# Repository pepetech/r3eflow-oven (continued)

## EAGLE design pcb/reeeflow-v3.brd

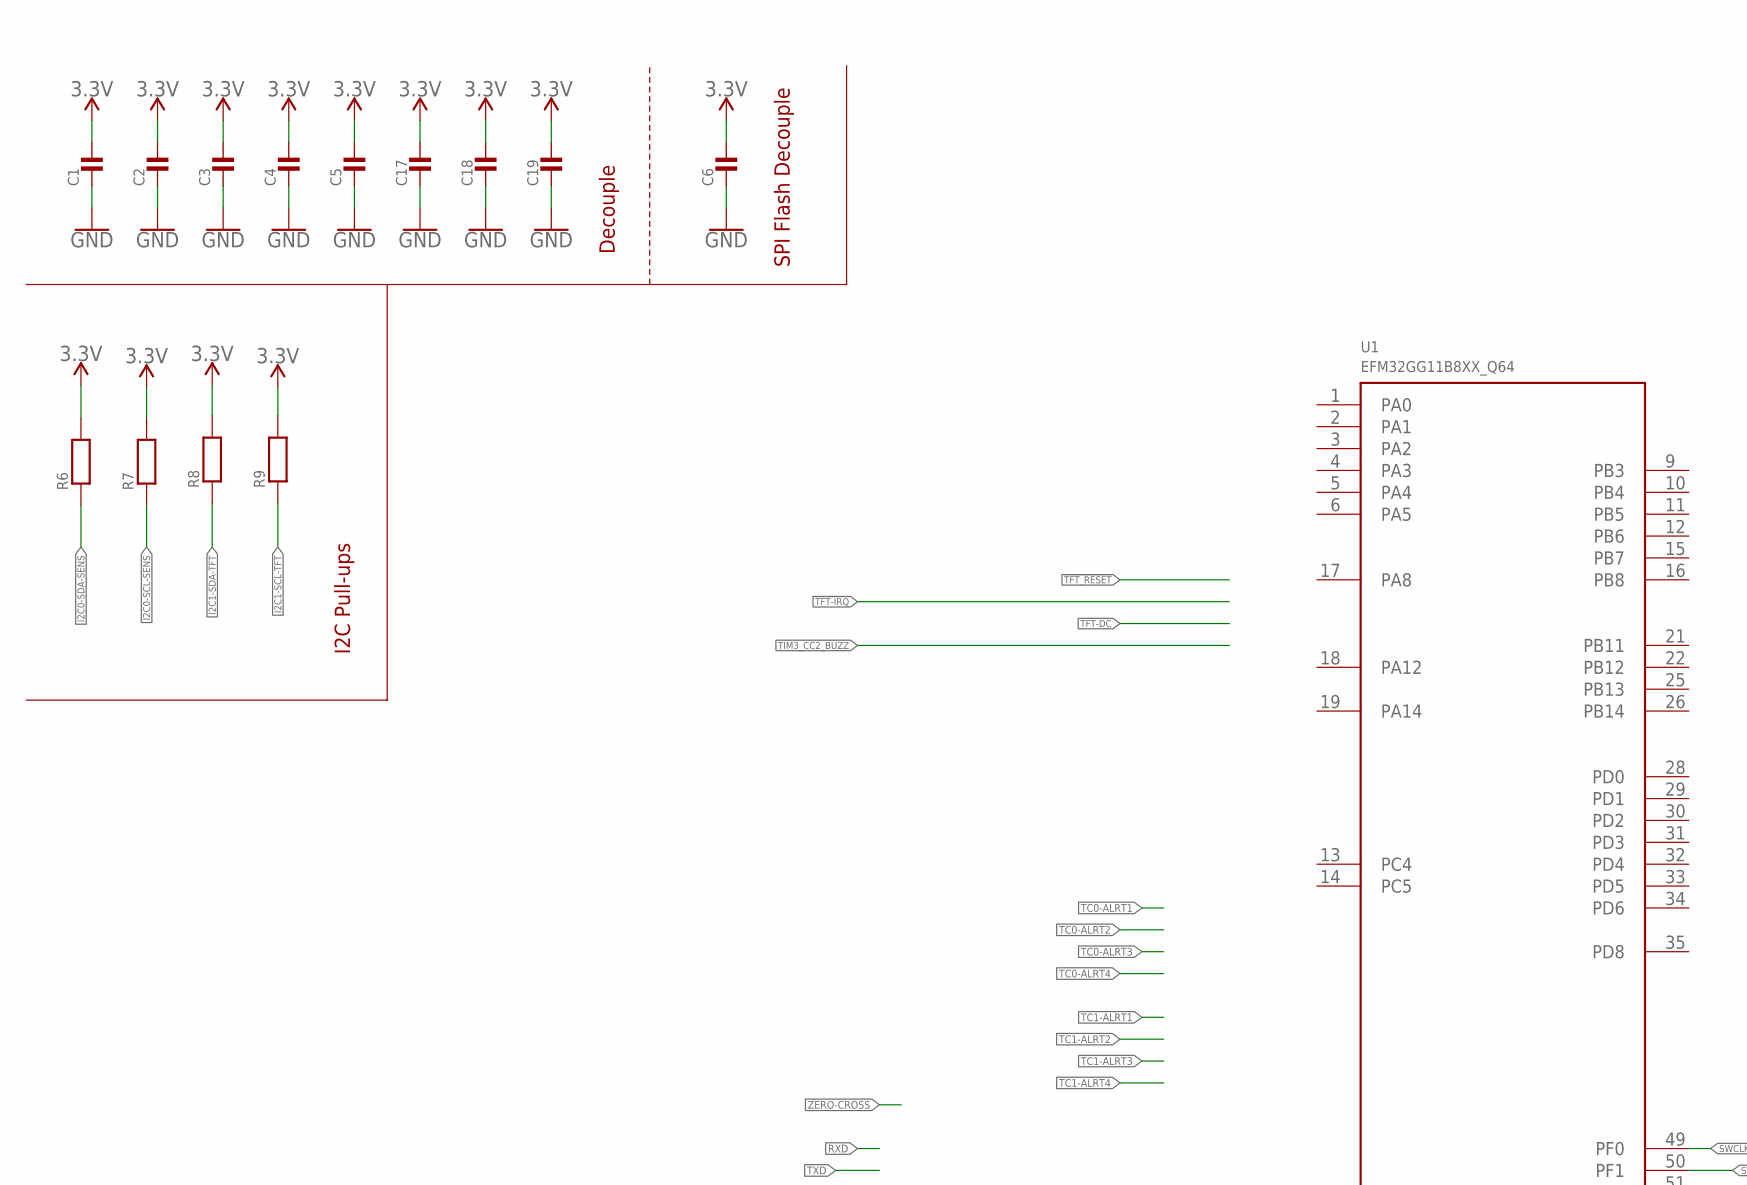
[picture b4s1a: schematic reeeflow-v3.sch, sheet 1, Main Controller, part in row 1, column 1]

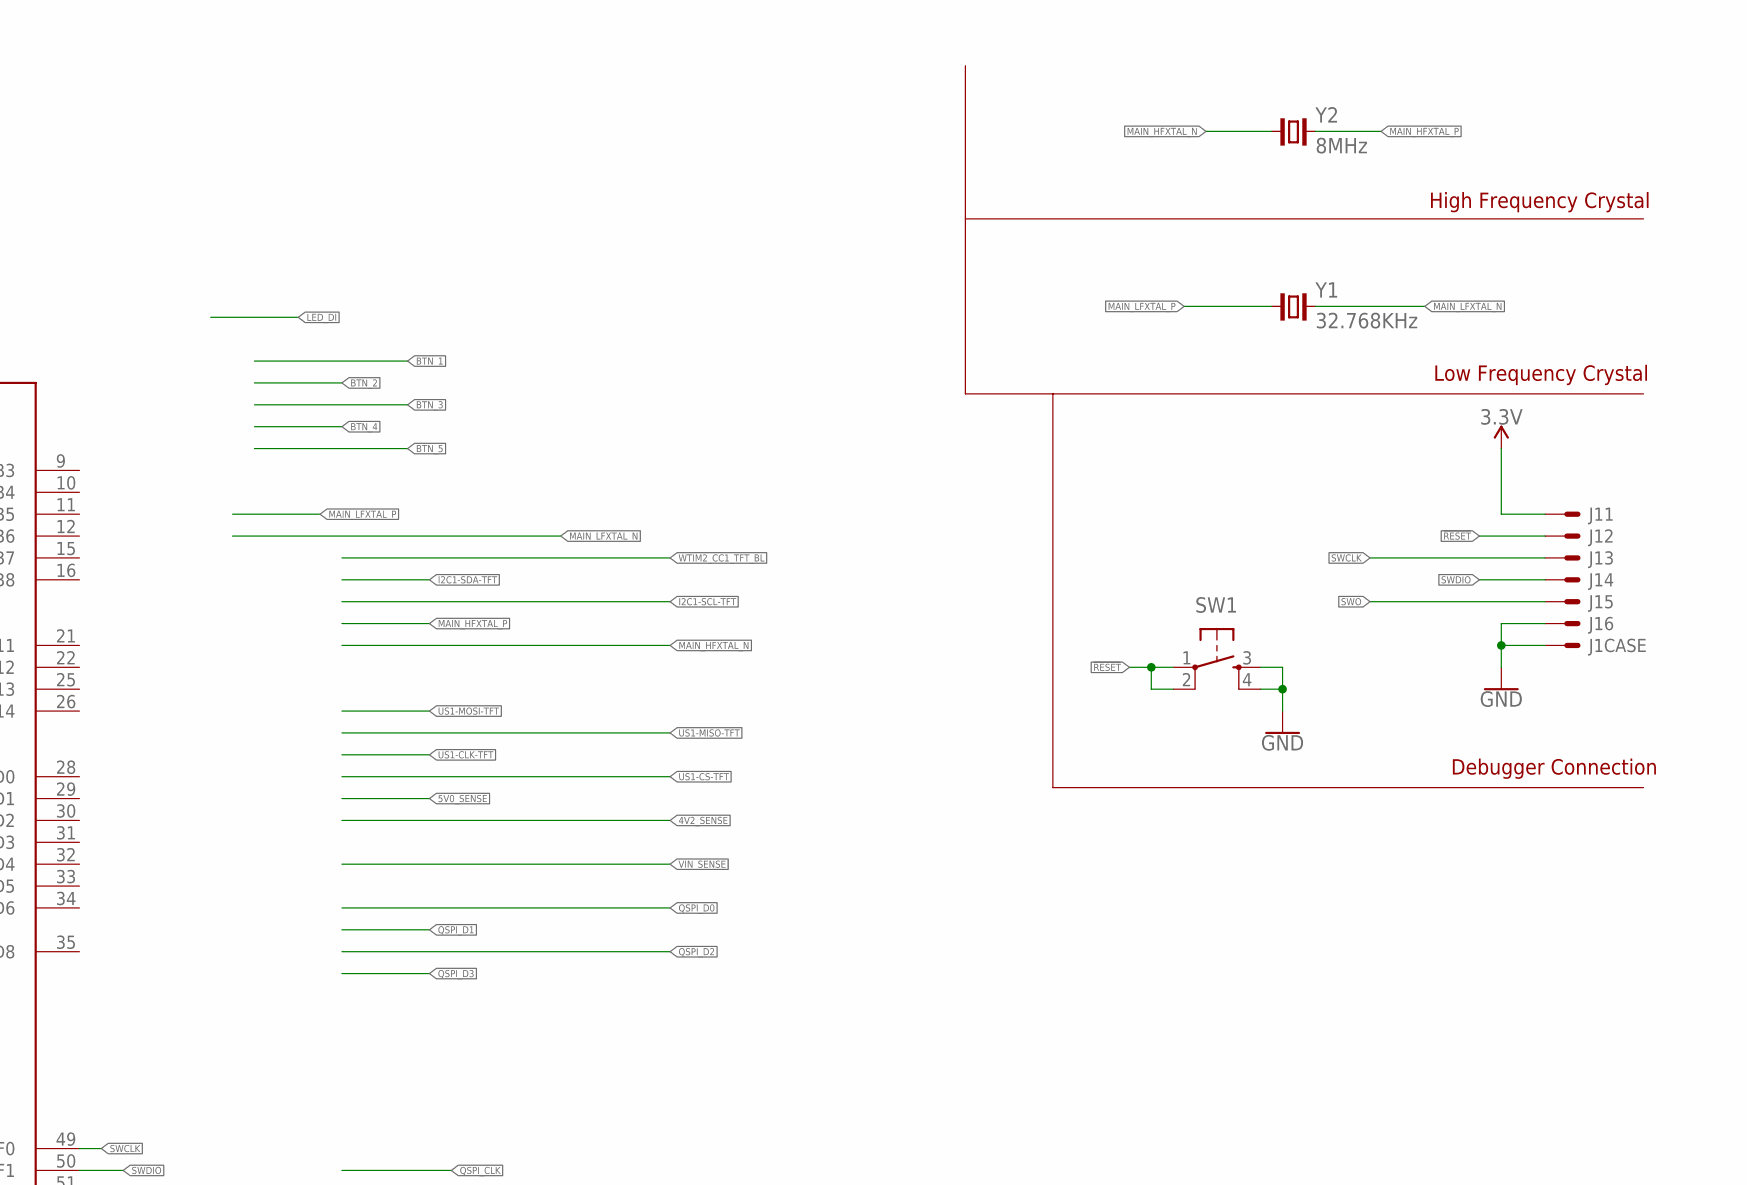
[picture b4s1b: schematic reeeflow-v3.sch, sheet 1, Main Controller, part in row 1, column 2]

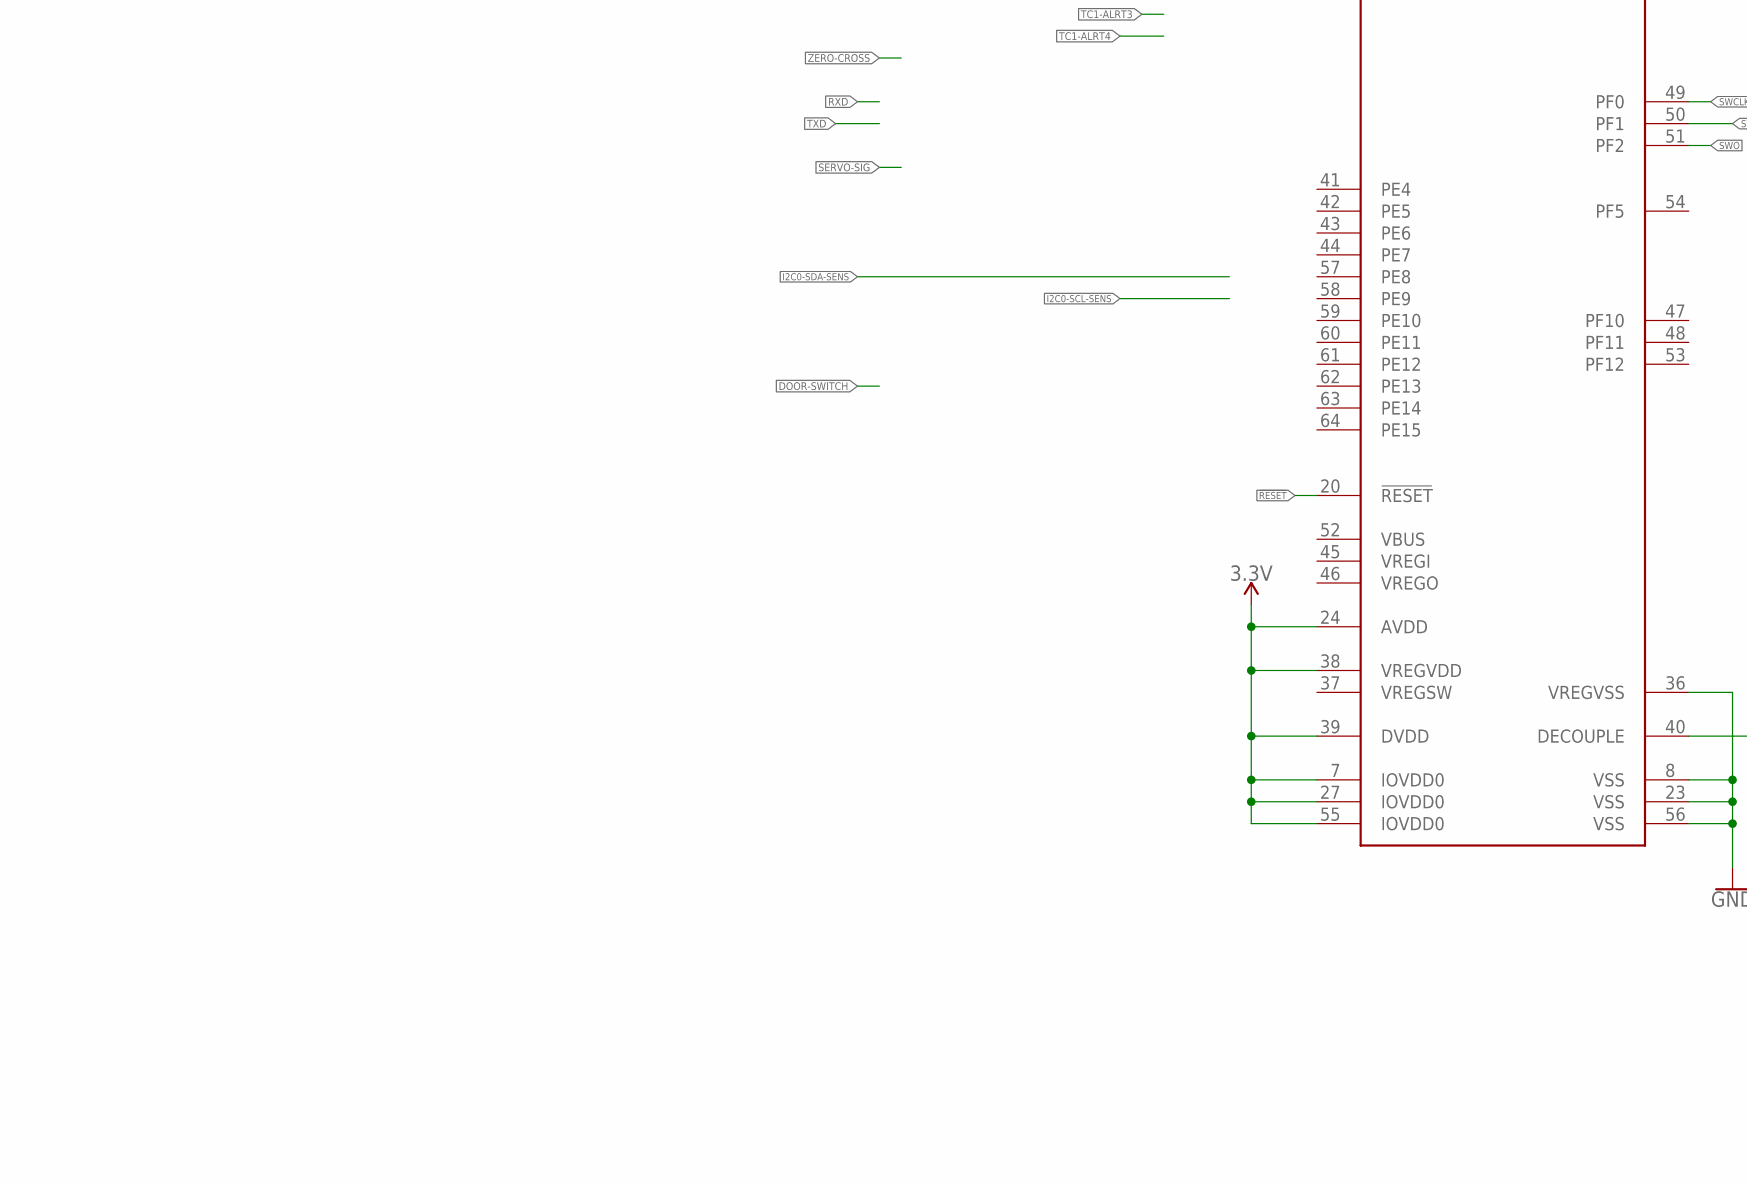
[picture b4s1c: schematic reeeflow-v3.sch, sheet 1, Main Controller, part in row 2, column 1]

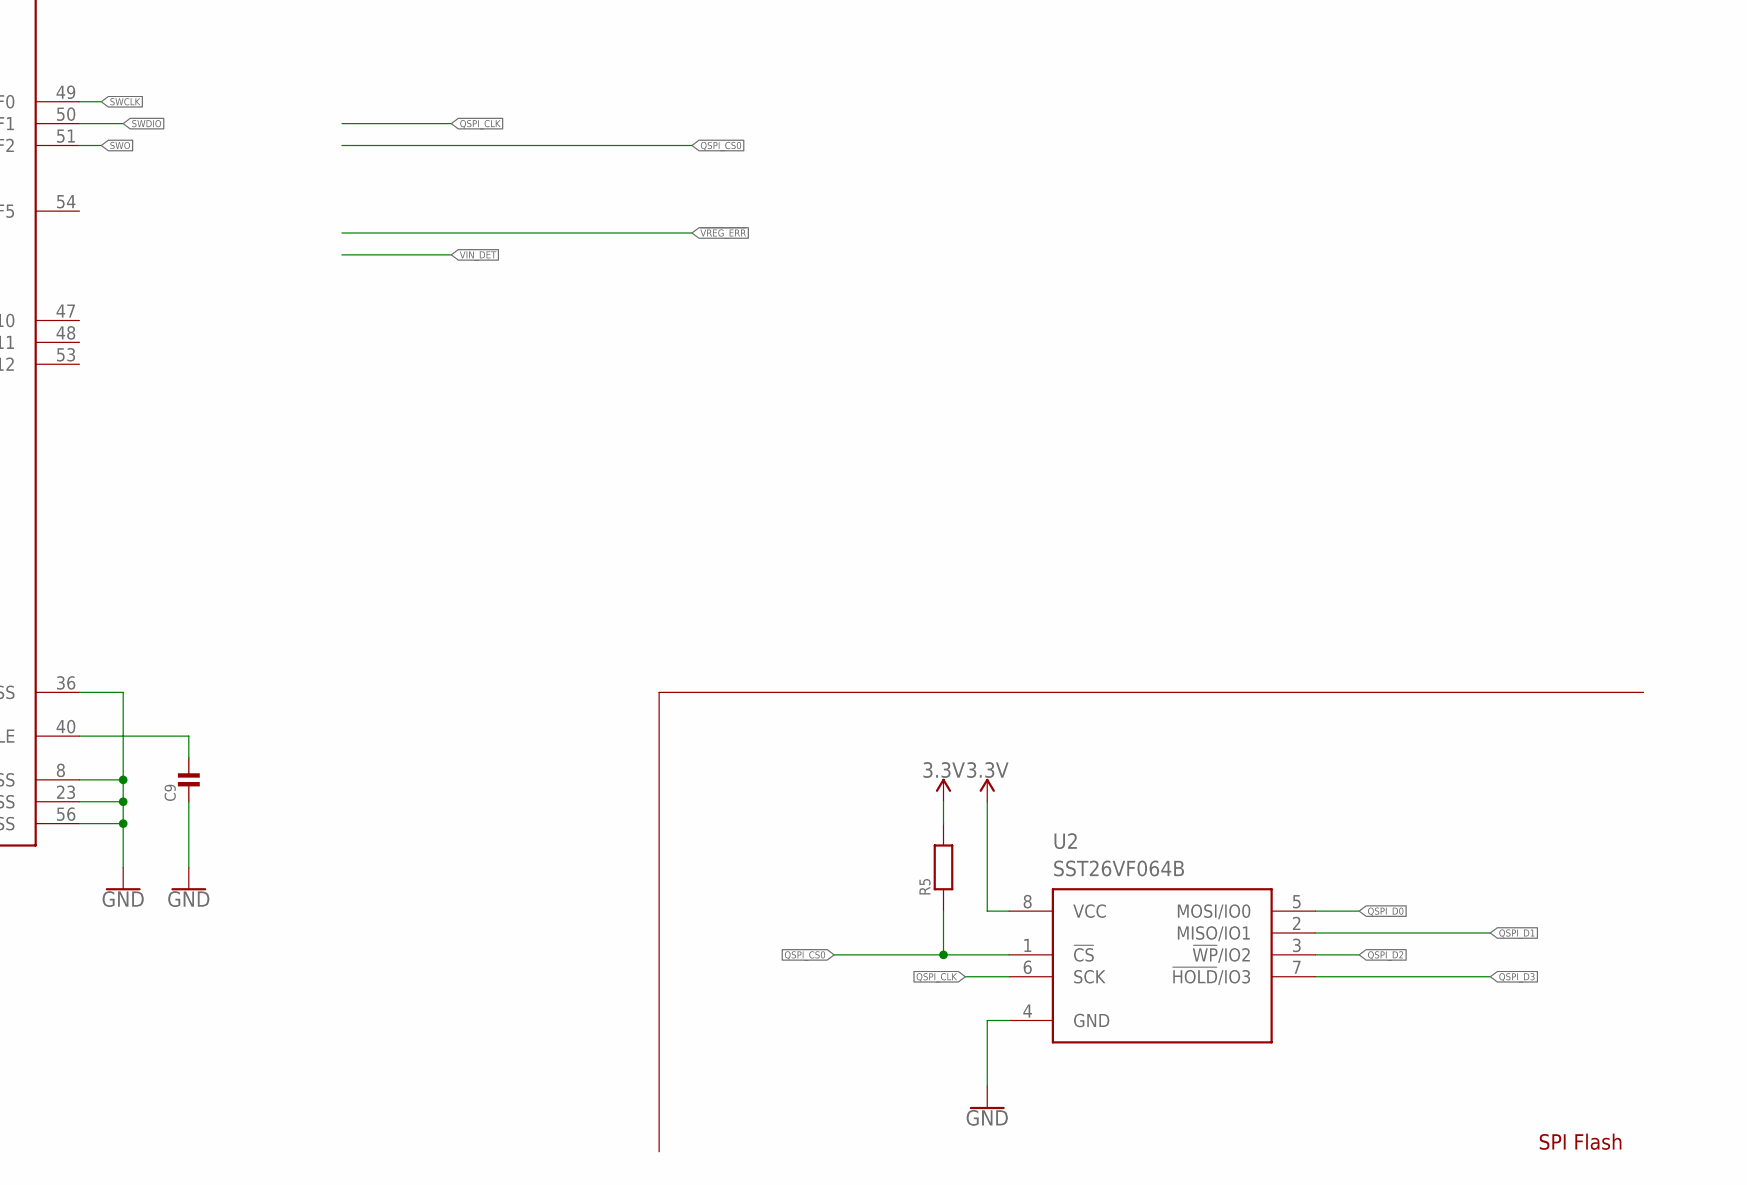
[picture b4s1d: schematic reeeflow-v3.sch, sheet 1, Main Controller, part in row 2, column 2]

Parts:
C1, C2, C3, C4, C5, C6, C9, C17, C18, C19: MLCC0603; 0603_WAVE
J1: SH-6; SM06B-SSR-H-TB
R5, R6, R7, R8, R9: RESISTOR0603; 0603_WAVE
SW1: PUSH_BUTTON
U1: EFM32GG11B8XX_Q64; QFP64
U2: SST26VF064B; WSOIC8
Y1: 32.768KHz; CM200S
Y2: 8MHz; 2-SMD-5X3

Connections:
3.3V: C1.P$1, C2.P$1, C3.P$1, C4.P$1, C5.P$1, C6.P$1, C17.P$1, C18.P$1, C19.P$1, J1.1, R5.P$2, R6.P$2, R7.P$2, R8.P$2, R9.P$2, U1.7 (IOVDD0), U1.24 (AVDD), U1.27 (IOVDD0), U1.38 (VREGVDD), U1.39 (DVDD), U1.55 (IOVDD0), U2.8 (VCC); also elsewhere on the board
!RESET: J1.2, SW1.1, SW1.2, U1.20 (!RESET)
GND: C1.P$2, C2.P$2, C3.P$2, C4.P$2, C5.P$2, C6.P$2, C9.P$2, C17.P$2, C18.P$2, C19.P$2, J1.6, J1.FIT@1, J1.FIT@2, SW1.3, SW1.4, U1.8 (VSS), U1.23 (VSS), U1.36 (VREGVSS), U1.56 (VSS), U2.4 (GND); also elsewhere on the board
I2C0-SCL-SENS: R7.P$1; also elsewhere on the board
I2C0-SDA-SENS: R6.P$1; also elsewhere on the board
I2C1-SCL-TFT: R9.P$1; also elsewhere on the board
I2C1-SDA-TFT: R8.P$1; also elsewhere on the board
MAIN_HFXTAL_N: Y2.1
MAIN_HFXTAL_P: Y2.2
MAIN_LFXTAL_N: Y1.4 (2)
MAIN_LFXTAL_P: Y1.1
unnamed: C9.P$1, U1.40 (DECOUPLE)
QSPI_CLK: U2.6 (SCK)
QSPI_CS0: R5.P$1, U2.1 (!CS!)
QSPI_D0: U2.5 (MOSI/IO0)
QSPI_D1: U2.2 (MISO/IO1)
QSPI_D2: U2.3 (!WP!/IO2)
QSPI_D3: U2.7 (!HOLD!/IO3)
SWCLK: J1.3, U1.49 (PF0)
SWDIO: J1.4, U1.50 (PF1)
SWO: J1.5, U1.51 (PF2)

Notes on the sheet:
High Frequency Crystal
Low Frequency Crystal
Decouple
I2C Pull-ups
Debugger Connection
SPI Flash
SPI Flash Decouple

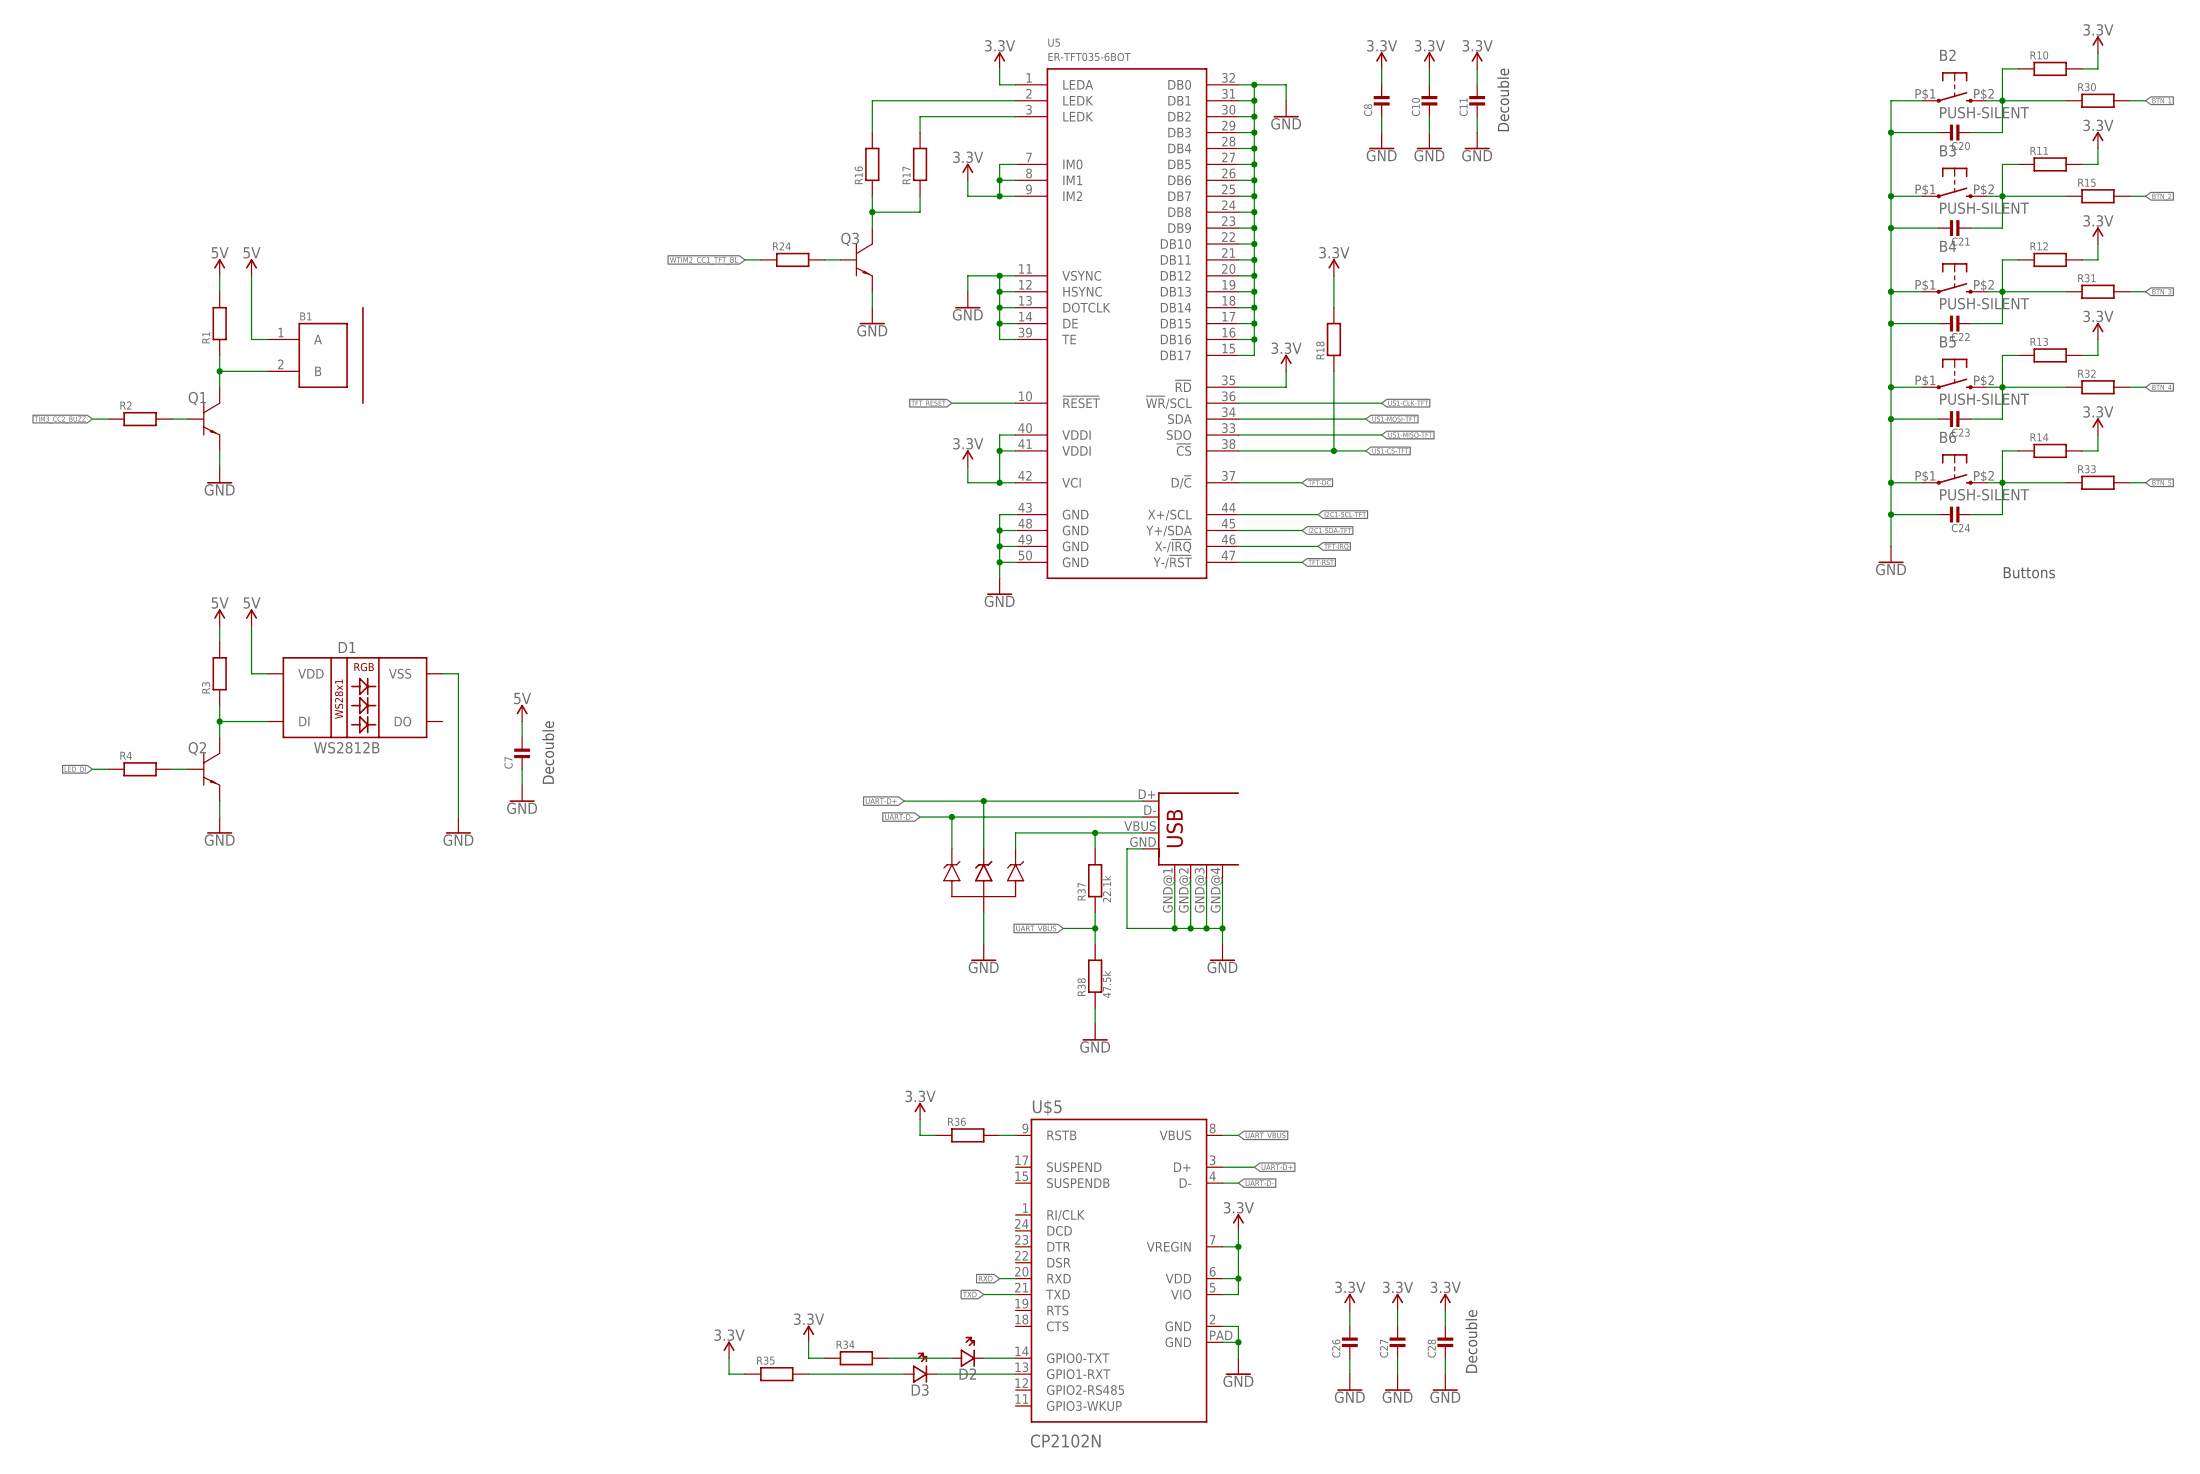
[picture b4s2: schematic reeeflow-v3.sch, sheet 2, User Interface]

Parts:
B1: PKLCS1212E2400-R1; BUZZ_PIEZO_SMD
B2, B3, B4, B5, B6: PUSH-SILENT; SILENT_BUT
C7, C8, C10, C11, C20, C21, C22, C23, C24, C26, C27, C28: MLCC0603; 0603_WAVE
D1: WS2812B
D2, D3: SML-D12; 0603_LED
D4: SP0503BAHT; SOT143
Q1, Q2, Q3: BC817-40; SOT-23-3
R1, R2, R3, R4, R10, R11, R12, R13, R14, R15, R16, R17, R18, R24, R30, R31, R32, R33, R34, R35, R36: RESISTOR0603; 0603_WAVE
R37: 22.1k; 0603_WAVE
R38: 47.5k; 0603_WAVE
U5: ER-TFT035-6BOT; ZIF50-TFT_BACK
U$5: CP2102N; QFN24
U$6: USB-SHIELD; USB-M-S1

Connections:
3.3V: C8.P$1, C10.P$1, C11.P$1, C26.P$1, C27.P$1, C28.P$1, R10.P$2, R11.P$2, R12.P$2, R13.P$2, R14.P$2, R18.P$2, R34.P$1, R35.P$1, R36.P$1, U5.1 (LEDA), U5.7 (IM0), U5.8 (IM1), U5.9 (IM2), U5.35 (!RD), U5.40 (VDDI), U5.41 (VDDI), U5.42 (VCI), U$5.5 (VIO), U$5.6 (VDD), U$5.7 (VREGIN); also elsewhere on the board
5V: B1.1 (A), C7.P$1, D1.1 (VDD), R1.P$2, R3.P$2; also elsewhere on the board
!TFT-IRQ: U5.46 (X-/!IRQ!)
!TFT-RST: U5.47 (Y-/!RST!)
!TFT_RESET: U5.10 (!RESET)
BTN_1: R30.P$2
BTN_2: R15.P$2
BTN_3: R31.P$2
BTN_4: R32.P$2
BTN_5: R33.P$2
GND: B2.P$1 (1), B3.P$1 (1), B4.P$1 (1), B5.P$1 (1), B6.P$1 (1), C7.P$2, C8.P$2, C10.P$2, C11.P$2, C20.P$1, C21.P$1, C22.P$1, C23.P$1, C24.P$1, C26.P$2, C27.P$2, C28.P$2, D1.3 (VSS), D4.1, Q1.P$2 (EM2), Q2.P$2 (EM2), Q3.P$2 (EM2), R38.P$1, U5.11 (VSYNC), U5.12 (HSYNC), U5.13 (DOTCLK), U5.14 (DE), U5.15 (DB17), U5.16 (DB16), U5.17 (DB15), U5.18 (DB14), U5.19 (DB13), U5.20 (DB12), U5.21 (DB11), U5.22 (DB10), U5.23 (DB9), U5.24 (DB8), U5.25 (DB7), U5.26 (DB6), U5.27 (DB5), U5.28 (DB4), U5.29 (DB3), U5.30 (DB2), U5.31 (DB1), U5.32 (DB0), U5.39 (TE), U5.43 (GND), U5.48 (GND), U5.49 (GND), U5.50 (GND), U$5.2 (GND), U$5.PAD (GND), U$6.GND, U$6.GND@1 (GND), U$6.GND@2 (GND), U$6.GND@3 (GND), U$6.GND@4 (GND); also elsewhere on the board
I2C1-SCL-TFT: U5.44 (X+/SCL); also elsewhere on the board
I2C1-SDA-TFT: U5.45 (Y+/SDA); also elsewhere on the board
LED_DI: R4.P$1
unnamed: B2.P$2 (3), C20.P$2, R10.P$1, R30.P$1
unnamed: D4.4, R37.P$2, U$6.VBUS
unnamed: B3.P$2 (3), C21.P$2, R11.P$1, R15.P$1
unnamed: B4.P$2 (3), C22.P$2, R12.P$1, R31.P$1
unnamed: Q2.P$1 (BA1), R4.P$2
unnamed: D1.4 (DI), Q2.P$3 (C03), R3.P$1
unnamed: B5.P$2 (3), C23.P$2, R13.P$1, R32.P$1
unnamed: D3.P$1 (CA), U$5.13 (GPIO1-RXT)
unnamed: B6.P$2 (3), C24.P$2, R14.P$1, R33.P$1
unnamed: D2.P$1 (CA), U$5.14 (GPIO0-TXT)
unnamed: D2.P$2 (AN), R34.P$2
unnamed: B1.2 (B), Q1.P$3 (C03), R1.P$1
unnamed: Q1.P$1 (BA1), R2.P$2
unnamed: D3.P$2 (AN), R35.P$2
unnamed: R16.P$2, U5.2 (LEDK)
unnamed: R17.P$2, U5.3 (LEDK)
unnamed: Q3.P$3 (C03), R16.P$1, R17.P$1
unnamed: Q3.P$1 (BA1), R24.P$2
unnamed: R36.P$2, U$5.9 (RSTB)
RXD: U$5.20 (RXD)
TFT-DC: U5.37 (D/!C!)
TIM3_CC2_BUZZ: R2.P$1
TXD: U$5.21 (TXD)
UART-D+: D4.3, U$5.3 (D+), U$6.D+
UART-D-: D4.2, U$5.4 (D-), U$6.D-
UART_VBUS: R37.P$1, R38.P$2, U$5.8 (VBUS)
US1-CLK-TFT: U5.36 (!WR!/SCL)
US1-CS-TFT: R18.P$1, U5.38 (!CS)
US1-MISO-TFT: U5.33 (SDO)
US1-MOSI-TFT: U5.34 (SDA)
WTIM2_CC1_TFT_BL: R24.P$1

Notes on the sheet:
Decouble
Buttons

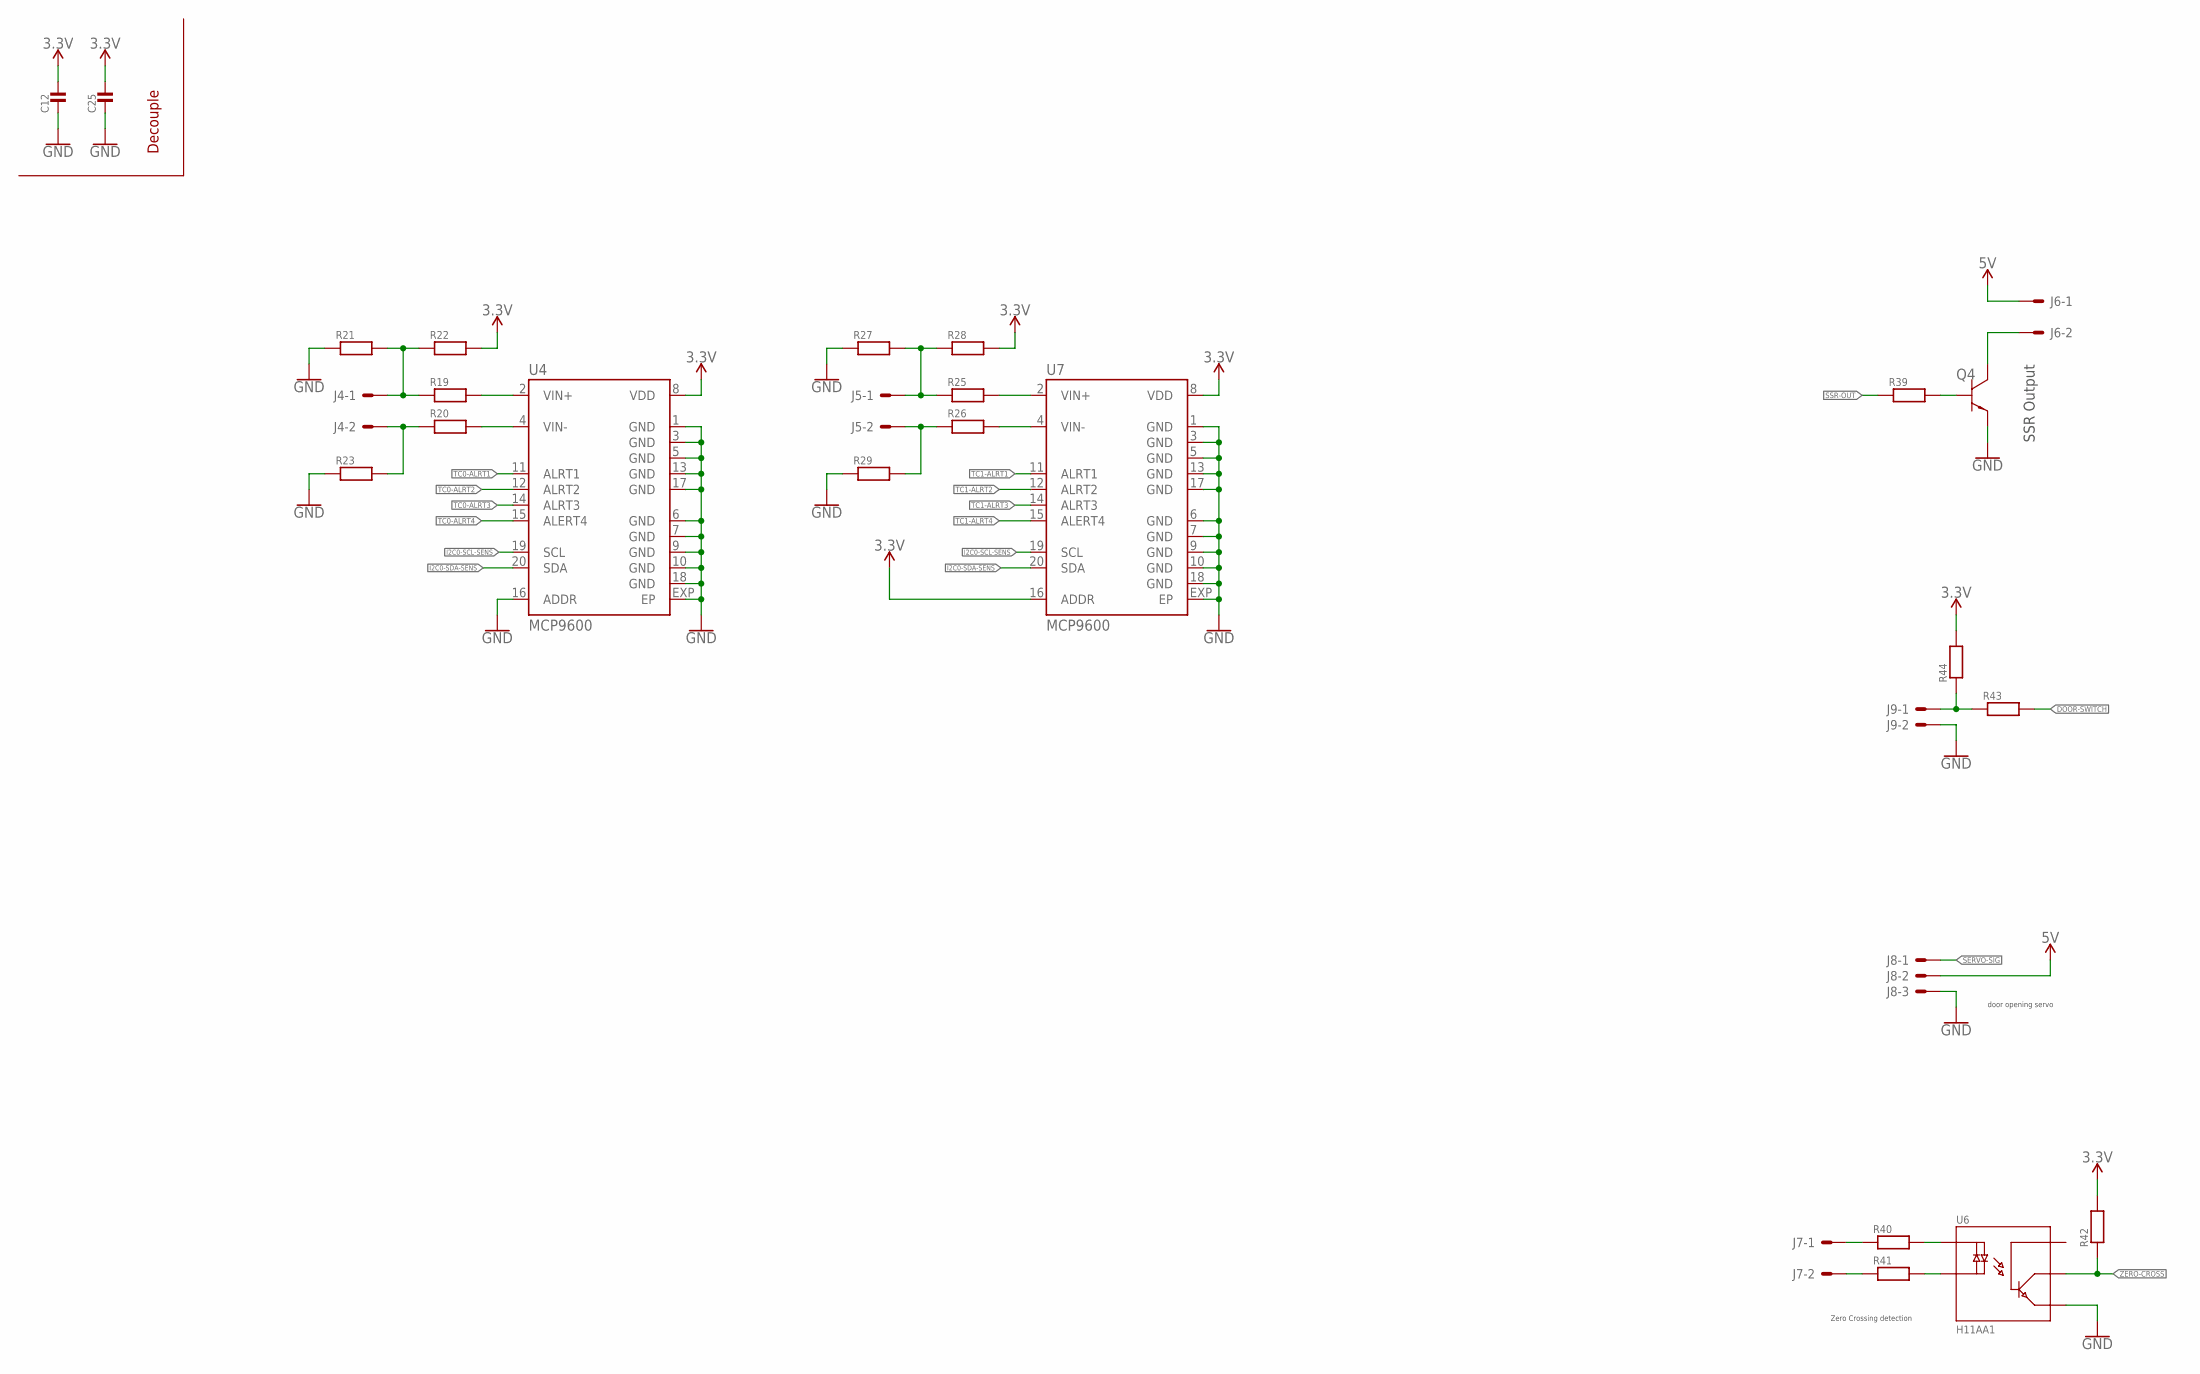
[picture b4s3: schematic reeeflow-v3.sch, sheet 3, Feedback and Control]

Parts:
C12, C25: MLCC0603; 0603_WAVE
J4, J5, J6, J7: 2EDG-2P
J8: 3X1_2.54
J9: 2X1_2.54
Q4: BC817-40; SOT-23-3
R19, R20, R21, R22, R23, R25, R26, R27, R28, R29, R39, R40, R41, R42, R43, R44: RESISTOR0603; 0603_WAVE
U4, U7: MCP9600; TQFN20-5X5
U6: H11AA1; DIP-6-SMD

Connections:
3.3V: C12.P$1, C25.P$1, R22.P$2, R28.P$2, R42.P$2, R44.P$2, U4.8 (VDD), U7.8 (VDD), U7.16 (ADDR); also elsewhere on the board
5V: J6.P$1, J8.P$2; also elsewhere on the board
DOOR-SWITCH: R43.P$2
GND: C12.P$2, C25.P$2, J8.P$3, Q4.P$2 (EM2), R21.P$1, R23.P$1, R27.P$1, R29.P$1, U4.1 (GND), U4.3 (GND), U4.5 (GND), U4.6 (GND), U4.7 (GND), U4.9 (GND), U4.10 (GND), U4.13 (GND), U4.16 (ADDR), U4.17 (GND), U4.18 (GND), U4.EXP (EP), U6.P$4 (E), U7.1 (GND), U7.3 (GND), U7.5 (GND), U7.6 (GND), U7.7 (GND), U7.9 (GND), U7.10 (GND), U7.13 (GND), U7.17 (GND), U7.18 (GND), U7.EXP (EP); also elsewhere on the board
I2C0-SCL-SENS: U4.19 (SCL), U7.19 (SCL); also elsewhere on the board
I2C0-SDA-SENS: U4.20 (SDA), U7.20 (SDA); also elsewhere on the board
unnamed: R25.P$2, U7.2 (VIN+)
unnamed: R26.P$2, U7.4 (VIN-)
unnamed: Q4.P$1 (BA1), R39.P$2
unnamed: J6.P$2, Q4.P$3 (C03)
unnamed: J7.P$1, R40.P$1
unnamed: R40.P$2, U6.P$1 (AC)
unnamed: R19.P$2, U4.2 (VIN+)
unnamed: R20.P$2, U4.4 (VIN-)
unnamed: R41.P$2, U6.P$2 (CA)
unnamed: J7.P$2, R41.P$1
unnamed: J9.1, R43.P$1, R44.P$1
SERVO-SIG: J8.P$1
SSR-OUT: R39.P$1
TC0-ALRT1: U4.11 (ALRT1)
TC0-ALRT2: U4.12 (ALRT2)
TC0-ALRT3: U4.14 (ALRT3)
TC0-ALRT4: U4.15 (ALERT4)
TC1-ALRT1: U7.11 (ALRT1)
TC1-ALRT2: U7.12 (ALRT2)
TC1-ALRT3: U7.14 (ALRT3)
TC1-ALRT4: U7.15 (ALERT4)
TC_VIN0+: J4.P$1, R19.P$1, R21.P$2, R22.P$1
TC_VIN0-: J4.P$2, R20.P$1, R23.P$2
TC_VIN1+: J5.P$1, R25.P$1, R27.P$2, R28.P$1
TC_VIN1-: J5.P$2, R26.P$1, R29.P$2
ZERO-CROSS: R42.P$1, U6.P$5 (C)

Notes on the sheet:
Decouple
SSR Output
Zero Crossing detection
door opening servo

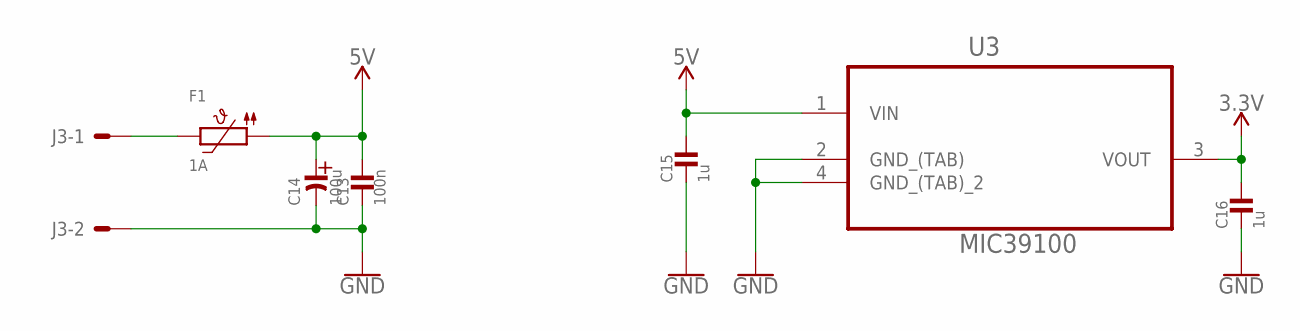
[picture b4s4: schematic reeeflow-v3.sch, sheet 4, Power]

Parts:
C13: 100n; 0603_WAVE
C14: 100u; 10X10-EL
C15, C16: 1u; 0603_WAVE
F1: 1A; PTC1812
J3: 2EDG-2P
U3: MIC39100; SOT230P700X180-4N

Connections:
3.3V: C16.P$1, U3.3 (VOUT); also elsewhere on the board
5V: C13.P$1, C14.AN, C15.P$1, F1.P$1 (1), U3.1 (VIN); also elsewhere on the board
GND: C13.P$2, C14.CAT (CA), C15.P$2, C16.P$2, J3.P$2, U3.2 (GND_(TAB)), U3.4 (GND_(TAB)_2); also elsewhere on the board
unnamed: F1.P$2 (2), J3.P$1

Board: 2 copper layers, 107 parts (8 on the bottom side), 53 nets, no tracks yet.

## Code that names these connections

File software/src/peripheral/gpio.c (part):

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                      | GPIO_P_MODEL_MODE2_DISABLED     // NR
                      | GPIO_P_MODEL_MODE3_INPUTPULLFILTER // TFT_IRQ
                      | GPIO_P_MODEL_MODE4_DISABLED     // NR
                      | GPIO_P_MODEL_MODE5_PUSHPULL     // TFT_RESET
                      | GPIO_P_MODEL_MODE6_PUSHPULL     // TFT_RST
                      | GPIO_P_MODEL_MODE7_DISABLED;    // MAIN_LFXTAL_P
    GPIO->P[1].MODEH  = GPIO_P_MODEH_MODE8_DISABLED     // MAIN_LFXTAL_N
                      | GPIO_P_MODEH_MODE9_DISABLED     // NR
                      | GPIO_P_MODEH_MODE10_DISABLED    // NR
                      | GPIO_P_MODEH_MODE11_WIREDANDPULLUPFILTER // I2C1-SDA-TTFT - Location 1
                      | GPIO_P_MODEH_MODE12_WIREDANDPULLUPFILTER // I2C1-SCL-TTFT - Location 1
                      | GPIO_P_MODEH_MODE13_DISABLED    // MAIN_HFXTAL_N
                      | GPIO_P_MODEH_MODE14_DISABLED    // MAIN_HFXTAL_P
                      | GPIO_P_MODEH_MODE15_DISABLED;   // NC
    GPIO->P[1].DOUT   = BIT(6) | BIT(11) | BIT(12);
    GPIO->P[1].OVTDIS = 0;
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
    // Debugger Route
    GPIO->ROUTEPEN &= ~(GPIO_ROUTEPEN_TDIPEN | GPIO_ROUTEPEN_TDOPEN); // Disable JTAG
    GPIO->ROUTEPEN |= GPIO_ROUTEPEN_SWVPEN; // Enable SWO
    GPIO->ROUTELOC0 = GPIO_ROUTELOC0_SWVLOC_LOC0; // SWO on PF2

    // External interrupts
    GPIO->EXTIPSELL = GPIO_EXTIPSELL_EXTIPSEL0_PORTB            // TFT_IRQ
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
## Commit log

2019-03-07 Stop tracking compilled binaries and add other gitignores
2019-03-08 added pid files
2019-03-08 added mcp9600.h modified pid variable names
2019-03-08 updated mcp9600.h
2019-03-08 Lamp dimmer
2019-03-08 Thermal pepe
2019-03-08 implemented mcp9600 funcs
2019-03-08 implented pid loop
2019-03-09 updated all
2019-03-09 added lookup table generation code
2019-03-09 Fix gay before it expands
2019-03-09 oops
2019-03-09 oops #2
2019-03-09 added pac_lookup.h
2019-03-09 updated main
2019-03-09 updated pid_init
2019-03-09 changed pac output clamping
2019-03-09 ima go sleep
2019-03-09 lol typo inicc
2019-03-09 Fix reee and add todo note
2019-03-09 Commenting
2019-03-10 added old eagle sch files in preparation for pcb design
2019-03-11 created new schematic ignore any and all cancer
2019-03-11 ignore eagle gay backup files
2019-03-11 pid testing
2019-03-11 I2C hell solved hopefully
2019-03-11 Add support for cross compilling
2019-03-11 Normalize I2C lib
2019-03-11 added support for multiple mcp9600 devices, reduced mcp9600 flag check frequency
2019-03-12 modified the sch slightly
2019-03-12 after lunch nap
2019-03-12 added cap to pid integral term
2019-03-12 add uart
2019-03-12 working on pcb
2019-03-13 pcb work
2019-03-13 updated gitignore
2019-03-15 first successful reflow!
2019-03-17 Update Makefile C++ compiller flags
2019-03-17 Change executable name to match new repository name Remove ST related tasks from the Makefile
2019-03-18 pn532 dev
2019-03-18 Add LDMA lib
2019-03-18 LDMA work
2019-03-18 uncommited pcb work
2019-03-19 rip pn532
2019-03-21 Add gitignore to .vscode folder
2019-03-21 Forgot to add
2019-03-22 reflow curve update
2019-04-03 Change .vscode gitignores
2019-04-06 syncro
2019-04-10 sync
2019-04-11 Change vscode intellisense to search on env variable
2019-04-21 Added human readable sizes option to makefile
2019-05-23 pcb v2 work
2019-05-24 pcb v2 done
2019-05-24 finished silkscreen and ssr pcb
2019-05-31 pcb order
2019-10-23 temporary lvgl port, compatibility changes for pcb v1
2019-10-24 lvgl driver modularity
2019-12-20 changed enviorenment variables
2019-12-20 Pulled down update to submodule_dir
2019-12-20 compile lvgl
2019-12-29 separate peripheral code
2019-12-30 code structuring
2020-01-02 project cleanup
2020-01-02 fix ili9488 lvgl color bug
2020-01-03 lvgl final implementation
2020-01-04 started implementing ui
2020-01-05 play sound non-blocking, ringled work, ui work
2020-01-05 ui work, non-blocking sound ok
2020-03-10 Case: base plate
2020-03-13 UI: added real time chart, and temperature display PROFILE: added linked list based profile
